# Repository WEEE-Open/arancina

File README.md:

# Arancina
The **Arancina** (**A**utonomous **R**AM **AN**alysis **CI**rcuit for **N**ot-broken **A**rrays) is a FPGA-based tool for testing the functionality of a DDR RAM, checking its characteristics and operating status through a series of test procedures.

The first prototype is built upon a Terasic [DE0-Nano](https://www.terasic.com.tw/cgi-bin/page/archive.pl?No=593) board, connected to an external DDR memory chip through a custom shield ([DDRacula](pcb/ddracula)), and using an LCD display and a bunch of buttons as user interface.

The tool is still **under heavy development** and not ready for use.

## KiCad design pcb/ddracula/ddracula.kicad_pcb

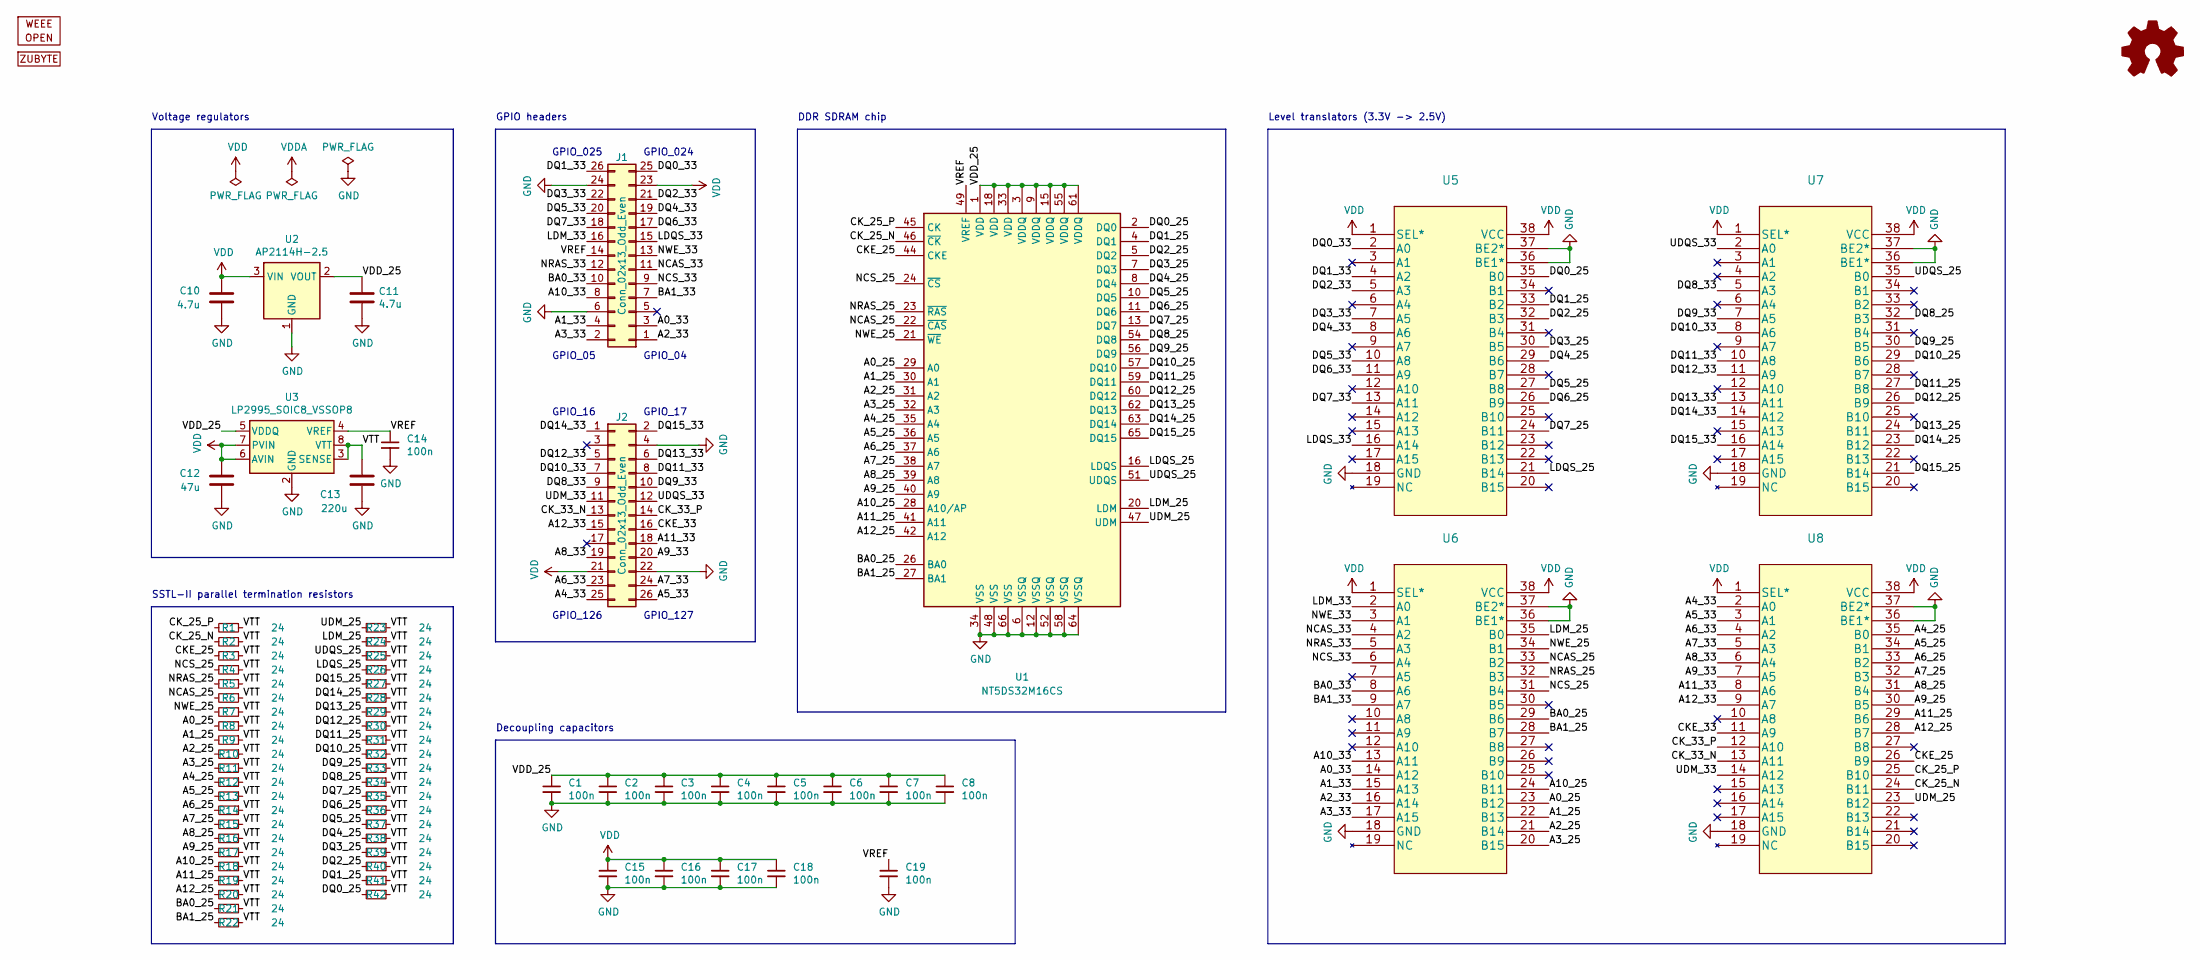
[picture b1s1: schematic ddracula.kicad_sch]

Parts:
C1, C2, C3, C4, C5, C6, C7, C8, C14, C15, C16, C17, C18, C19: 100n; C_0402_1005Metric
C10, C11: 4.7u; C_0805_2012Metric
C12: 47u; C_0805_2012Metric
C13: 220u; C_1206_3216Metric
J1, J2: Conn_02x13_Odd_Even; PinSocket_2x13_P2.54mm_Vertical
LOGO1: WEEE_Open; Logo_WO_First_Letter
LOGO2: Zubyte; Logo_Zubyte
LOGO3: Logo_Open_Hardware_Small; OSHW-Logo_5.7x6mm_SilkScreen
R1, R2, R3, R4, R5, R6, R7, R8, R9, R10, R11, R12, R13, R14, R15, R16, R17, R18, R19, R20, R21, R22, R23, R24, R25, R26, R27, R28, R29, R30, R31, R32, R33, R34, R35, R36, R37, R38, R39, R40, R41, R42: 24; R_0402_1005Metric
U1: NT5DS32M16CS; TSOP-II-66_22.2x10.16mm_P0.8mm
U2: AP2114H-2.5; SOT-223
U3: LP2995_SOIC8_VSSOP8; SOIC-8_3.9x4.9mm_P1.27mm
U5, U6, U7, U8: (no value)

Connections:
/A0_25: R8.2, U1.29 (A0), U6.23 (B12)
/A0_33: J1.3, U6.14 (A12)
/A1_25: R9.2, U1.30 (A1), U6.22 (B13)
/A1_33: J1.4, U6.15 (A13)
/A2_25: R10.2, U1.31 (A2), U6.21 (B14)
/A2_33: J1.1, U6.16 (A14)
/A3_25: R11.2, U1.32 (A3), U6.20 (B15)
/A3_33: J1.2, U6.17 (A15)
/A4_25: R12.2, U1.35 (A4), U8.35 (B0)
/A4_33: J2.25, U8.2 (A0)
/A5_25: R13.2, U1.36 (A5), U8.34 (B1)
/A5_33: J2.26, U8.3 (A1)
/A6_25: R14.2, U1.37 (A6), U8.33 (B2)
/A6_33: J2.23, U8.4 (A2)
/A7_25: R15.2, U1.38 (A7), U8.32 (B3)
/A7_33: J2.24, U8.5 (A3)
/A8_25: R16.2, U1.39 (A8), U8.31 (B4)
/A8_33: J2.19, U8.6 (A4)
/A9_25: R17.2, U1.40 (A9), U8.30 (B5)
/A9_33: J2.20, U8.7 (A5)
/A10_25: R18.2, U1.28 (A10/AP), U6.24 (B11)
/A10_33: J1.8, U6.13 (A11)
/A11_25: R19.2, U1.41 (A11), U8.29 (B6)
/A11_33: J2.18, U8.8 (A6)
/A12_25: R20.2, U1.42 (A12), U8.28 (B7)
/A12_33: J2.15, U8.9 (A7)
/BA0_25: R21.2, U1.26 (BA0), U6.29 (B6)
/BA0_33: J1.10, U6.8 (A6)
/BA1_25: R22.2, U1.27 (BA1), U6.28 (B7)
/BA1_33: J1.7, U6.9 (A7)
/CKE_25: R3.2, U1.44 (CKE), U8.26 (B9)
/CKE_33: J2.16, U8.11 (A9)
/CK_25_N: R2.2, U1.46 (~CK), U8.24 (B11)
/CK_25_P: R1.2, U1.45 (CK), U8.25 (B10)
/CK_33_N: J2.13, U8.13 (A11)
/CK_33_P: J2.14, U8.12 (A10)
/DQ0_25: R42.2, U1.2 (DQ0), U5.35 (B0)
/DQ0_33: J1.25, U5.2 (A0)
/DQ1_25: R41.2, U1.4 (DQ1), U5.33 (B2)
/DQ1_33: J1.26, U5.4 (A2)
/DQ2_25: R40.2, U1.5 (DQ2), U5.32 (B3)
/DQ2_33: J1.21, U5.5 (A3)
/DQ3_25: R39.2, U1.7 (DQ3), U5.30 (B5)
/DQ3_33: J1.22, U5.7 (A5)
/DQ4_25: R38.2, U1.8 (DQ4), U5.29 (B6)
/DQ4_33: J1.19, U5.8 (A6)
/DQ5_25: R37.2, U1.10 (DQ5), U5.27 (B8)
/DQ5_33: J1.20, U5.10 (A8)
/DQ6_25: R36.2, U1.11 (DQ6), U5.26 (B9)
/DQ6_33: J1.17, U5.11 (A9)
/DQ7_25: R35.2, U1.13 (DQ7), U5.24 (B11)
/DQ7_33: J1.18, U5.13 (A11)
/DQ8_25: R34.2, U1.54 (DQ8), U7.32 (B3)
/DQ8_33: J2.9, U7.5 (A3)
/DQ9_25: R33.2, U1.56 (DQ9), U7.30 (B5)
/DQ9_33: J2.10, U7.7 (A5)
/DQ10_25: R32.2, U1.57 (DQ10), U7.29 (B6)
/DQ10_33: J2.7, U7.8 (A6)
/DQ11_25: R31.2, U1.59 (DQ11), U7.27 (B8)
/DQ11_33: J2.8, U7.10 (A8)
/DQ12_25: R30.2, U1.60 (DQ12), U7.26 (B9)
/DQ12_33: J2.5, U7.11 (A9)
/DQ13_25: R29.2, U1.62 (DQ13), U7.24 (B11)
/DQ13_33: J2.6, U7.13 (A11)
/DQ14_25: R28.2, U1.63 (DQ14), U7.23 (B12)
/DQ14_33: J2.1, U7.14 (A12)
/DQ15_25: R27.2, U1.65 (DQ15), U7.21 (B14)
/DQ15_33: J2.2, U7.16 (A14)
/LDM_25: R24.2, U1.20 (LDM), U6.35 (B0)
/LDM_33: J1.16, U6.2 (A0)
/LDQS_25: R26.2, U1.16 (LDQS), U5.21 (B14)
/LDQS_33: J1.15, U5.16 (A14)
/NCAS_25: R6.2, U1.22 (~CAS), U6.33 (B2)
/NCAS_33: J1.11, U6.4 (A2)
/NCS_25: R4.2, U1.24 (~CS), U6.31 (B4)
/NCS_33: J1.9, U6.6 (A4)
/NRAS_25: R5.2, U1.23 (~RAS), U6.32 (B3)
/NRAS_33: J1.12, U6.5 (A3)
/NWE_25: R7.2, U1.21 (~WE), U6.34 (B1)
/NWE_33: J1.13, U6.3 (A1)
/UDM_25: R23.2, U1.47 (UDM), U8.23 (B12)
/UDM_33: J2.11, U8.14 (A12)
/UDQS_25: R25.2, U1.51 (UDQS), U7.35 (B0)
/UDQS_33: J2.12, U7.2 (A0)
/VDD_25: C1.1, C2.1, C3.1, C4.1, C5.1, C6.1, C7.1, C8.1, C11.1, U1.1 (VDD), U1.3 (VDDQ), U1.9 (VDDQ), U1.15 (VDDQ), U1.18 (VDD), U1.33 (VDD), U1.55 (VDDQ), U1.61 (VDDQ), U2.2 (VOUT), U2.4 (VOUT), U3.5 (VDDQ)
/VREF: C14.1, C19.1, J1.14, U1.49 (VREF), U3.4 (VREF)
/VTT: C13.2, R1.1, R2.1, R3.1, R4.1, R5.1, R6.1, R7.1, R8.1, R9.1, R10.1, R11.1, R12.1, R13.1, R14.1, R15.1, R16.1, R17.1, R18.1, R19.1, R20.1, R21.1, R22.1, R23.1, R24.1, R25.1, R26.1, R27.1, R28.1, R29.1, R30.1, R31.1, R32.1, R33.1, R34.1, R35.1, R36.1, R37.1, R38.1, R39.1, R40.1, R41.1, R42.1, U3.3 (SENSE), U3.8 (VTT)
GND: C1.2, C2.2, C3.2, C4.2, C5.2, C6.2, C7.2, C8.2, C10.1, C11.2, C12.1, C13.1, C14.2, C15.2, C16.2, C17.2, C18.2, C19.2, J1.6, J1.24, J2.4, J2.22, U1.6 (VSSQ), U1.12 (VSSQ), U1.34 (VSS), U1.48 (VSS), U1.52 (VSSQ), U1.58 (VSSQ), U1.64 (VSSQ), U1.66 (VSS), U2.1 (GND), U3.2 (GND), U5.18 (GND), U5.36 (BE1*), U5.37 (BE2*), U6.18 (GND), U6.36 (BE1*), U6.37 (BE2*), U7.18 (GND), U7.36 (BE1*), U7.37 (BE2*), U8.18 (GND), U8.36 (BE1*), U8.37 (BE2*)
VDD: C10.2, C12.2, C15.1, C16.1, C17.1, C18.1, J1.23, J2.21, U2.3 (VIN), U3.6 (AVIN), U3.7 (PVIN), U5.1 (SEL*), U5.38 (VCC), U6.1 (SEL*), U6.38 (VCC), U7.1 (SEL*), U7.38 (VCC), U8.1 (SEL*), U8.38 (VCC)

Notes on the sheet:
GPIO_04
GPIO_05
Level translators (3.3V -> 2.5V)
SSTL-II parallel termination resistors
GPIO_025
GPIO_126
DDR SDRAM chip
GPIO headers
Voltage regulators
Decoupling capacitors
GPIO_024
GPIO_16
GPIO_17
GPIO_127

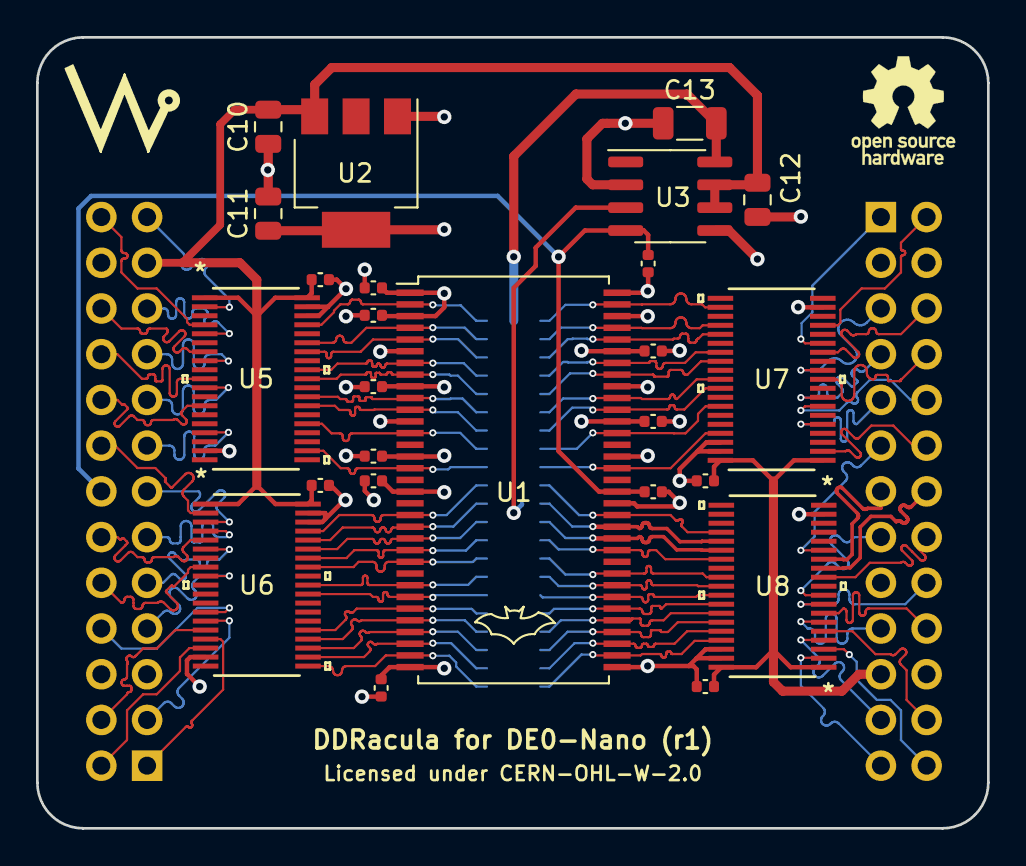
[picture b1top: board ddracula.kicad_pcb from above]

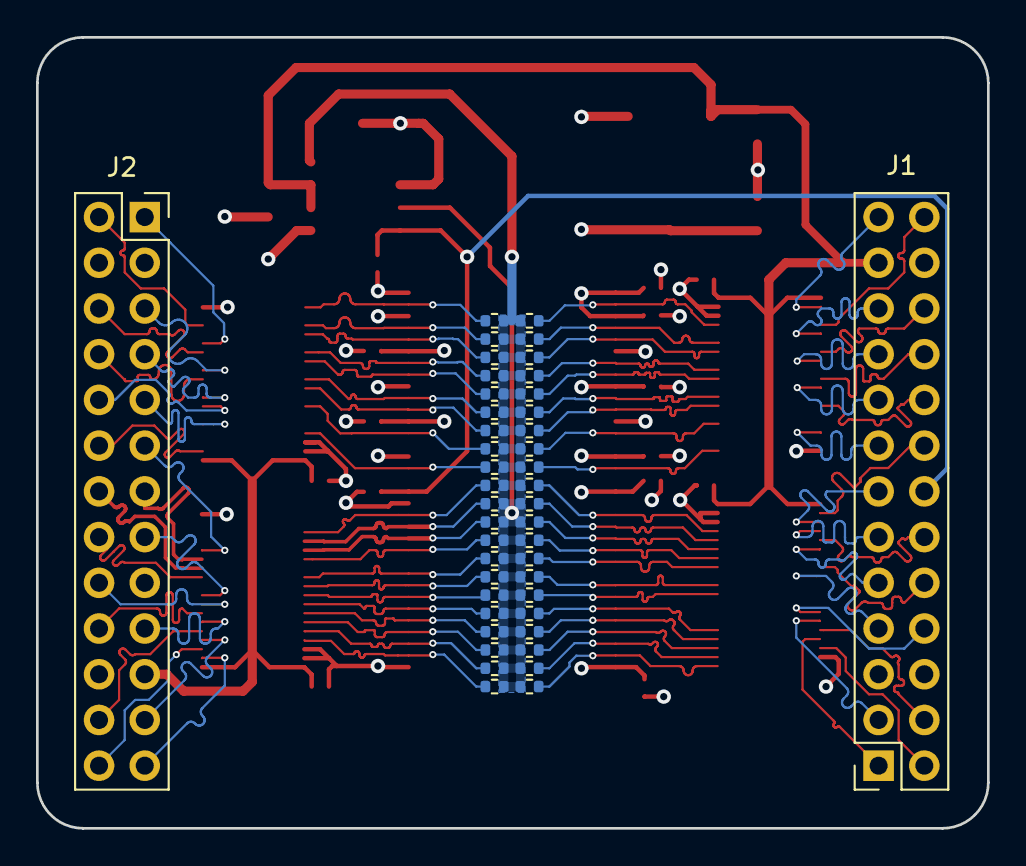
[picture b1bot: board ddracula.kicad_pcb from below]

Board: 4 copper layers, 52.8 x 43.9 mm, 72 parts (44 on the bottom side), 89 nets.

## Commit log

2020-11-01 Add refresh module
2020-11-01 Add Output Module
2020-11-01 Shorten DQS delay line
    Delay line was one falling-edge too long. One of the flipflops has been removed, effectively making DQS_DELAY the number of falling edges after the enable signal has been sampled after which DDR_DQS 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
2020-11-01 Add DDR Memory simulation circuit
2020-11-01 Add documentation folder
2020-11-01 Add SDR to DDR interface components
2020-11-01 Rename output port
2020-11-01 Remove old file
2020-11-01 Remove old files
2020-11-01 Add testing folder
2020-11-01 Edit bad gitignore
2020-11-01 Add testbench for OutputModule
2020-11-01 Add gitignores
2020-11-01 Change DQS delay line reset to asynchronous
    Now the delay line has an asynchronous reset, avoiding the need to wait for DQS_DELAY clock cycles before issuing an OE
2020-11-01 Fix syntax errors
2023-04-06 First commit (LCD Test)

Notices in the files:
pcb/ddracula/ddracula.kicad_pcb:
Licensed under CERN-OHL-W-2.0
parts and their libraries:
Copyright 2016 Accelerated Designs. All rights reserved.
